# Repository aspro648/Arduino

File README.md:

# Arduino
DIY Clones done in KiCAD

- [Uno Compatible Through Hole](DIY%20Arduino/Arduino)
- [Leonardo Compatible Surface Mount](Leonardo/)

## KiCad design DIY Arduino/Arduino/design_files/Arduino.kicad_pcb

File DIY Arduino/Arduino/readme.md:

DIY Arduino clone done in KiCad.

You will need to build a FTDI breakout board using a FT231XQ QFN20 chip with a pinout matching the FT231XS (SSOP-20), but in a DIP-20 spacing.  It is all downhill from there!

Bill Of Materials
----------------
- 1 ea., DIY Arduino PCB from kicad.pcb file.
- 1 ea., FT231x breakout PCB from kicad.pcb file.
- 1 ea., U1 L7805CV IC REG LINEAR 5V 1.5A TO220AB, https://www.digikey.com/short/jn9qzp
- 1 ea., U2 FT231XQ 20QFN, https://www.digikey.com/short/jn57wn
- 1 ea., U3 SN74LS125AN, IC BUF NON-INVERT 5.25V 14DIP, https://www.digikey.com/short/jn973j
- 1 ea., U4 MCP1700-3302E/TO IC REG LINEAR 3.3V 250MA TO92-3, https://www.digikey.com/short/jn9q57
- 1 ea., U5 Atmega328P-PU https://www.digikey.com/short/jn57wj
- 1 ea., Y1 CER RES 16.0000MHZ 30PF T/H, ECS ZTT-16.00MX, https://www.digikey.com/short/jn9pjv
- 1 ea., C1 0.33uF 50V electrolytic Capacitor 2.5mm lead spacing, Nichicon 	UMT1HR33MDD1TP, https://www.digikey.com/short/jddb2h
- 4 ea., C2 - 5 CAP CER 0.1UF 25V Y5V RADIAL 2.5mm lead spacing, Vishay K104Z15Y5VE5TL2, https://www.digikey.com/short/jn9pm2
- 3 ea., C6 - 8 CAP CER 1UF 25V X7R RADIAL 5mm lead spacing, TDK FG28X7R1E105KRT06, https://www.digikey.com/short/jn9p97
- 1 ea., R1 4K7 Ohm Resistors 1/4 W 5%, https://www.digikey.com/short/jn5tmq
- 2 ea., R2, R13 1K Ohm Resistors 1/4 W 5%, https://www.digikey.com/short/jn5t4d
- 2 ea., R3 - 4 470 Ohm Resistors 1/4 W 5%, https://www.digikey.com/short/jn5tmp
- 2 ea., R5 - 6 22 Ohm Resistors 1/4 W 5%, https://www.digikey.com/short/jd0wcj
- 2 ea., R7 - 8 10K Resistors 1/4 W 5%, https://www.digikey.com/short/jn5t41
- 1 ea., D1 DIODE SCHOTTKY 40V 2A DO15, SMC SB240TA, https://www.digikey.com/short/jn57cv
- 1 ea., D2 (Power) Green 3mm LED 5.6mcd, LiteOn LTL-4231N https://www.digikey.com/short/jn5tr0
- 1 ea., D13 (D13) Red 3mm LED 4.4mcd, LiteOn LTL-4211N, https://www.digikey.com/short/jn5trr
- 2 ea., D3, D4 (TX/RX) Yellow 3mm LED 6.7mcd, LiteOn LTL-4251, https://www.digikey.com/short/jn5t5f
- 1 ea., F1 PTC RESET FUSE 30V 700MA RADIAL, Littlefuse RHEF070-2, https://www.digikey.com/short/pq0mtz
- 1 ea., J1 USB B Connector, Pulse E8144-B02022-L, https://www.digikey.com/short/jn571j
- 1 ea., J2 Barrel Jack 2.1mm, CUI 	PJ-202AH https://www.digikey.com/short/jd0wz3
- 2 ea., P1, P3 8-Pin header, https://www.digikey.com/short/jwj4dp
- 1 ea., P2 6-Pin header, https://www.digikey.com/short/jwj4w4
- 1 ea., P3 10-Pin header, https://www.digikey.com/short/jwj4n7
- 4 ea., Rubber feet, https://www.digikey.com/short/jntvm1 or https://www.digikey.com/short/jntvbz
- 1 ea., Pinheader, S1012EC-40-ND, https://www.digikey.com/short/7382z2
- 1 ea., CONN JUMPER SHORTING .100" GOLD, Sullins NPC02SXON-RC, https://www.digikey.com/short/jn5t0j
- 1 ea., 28 Pin socket, On Shore ED281DT, https://www.digikey.com/short/jn5tz5
- 1 ea., 20 Pin socket, On Shore ED20DT, https://www.digikey.com/short/jn5tzm
- 1 ea., 14 Pin socket, On Shore ED14DT, https://www.digikey.com/short/jn5tp1

License
----------------
[Attribution-ShareAlike 3.0 United States (CC BY-SA 3.0 US)](https://creativecommons.org/licenses/by-sa/3.0/us/)

You are free to:

- Share — copy and redistribute the material in any medium or format
- Adapt — remix, transform, and build upon the material

Under the following terms:

- Attribution — You must give appropriate credit, provide a link to the license, and indicate if changes were made. You may do so in any reasonable manner, but not in any way that suggests the licensor endorses you or your use.
- ShareAlike — If you remix, transform, or build upon the material, you must distribute your contributions under the same license as the original.

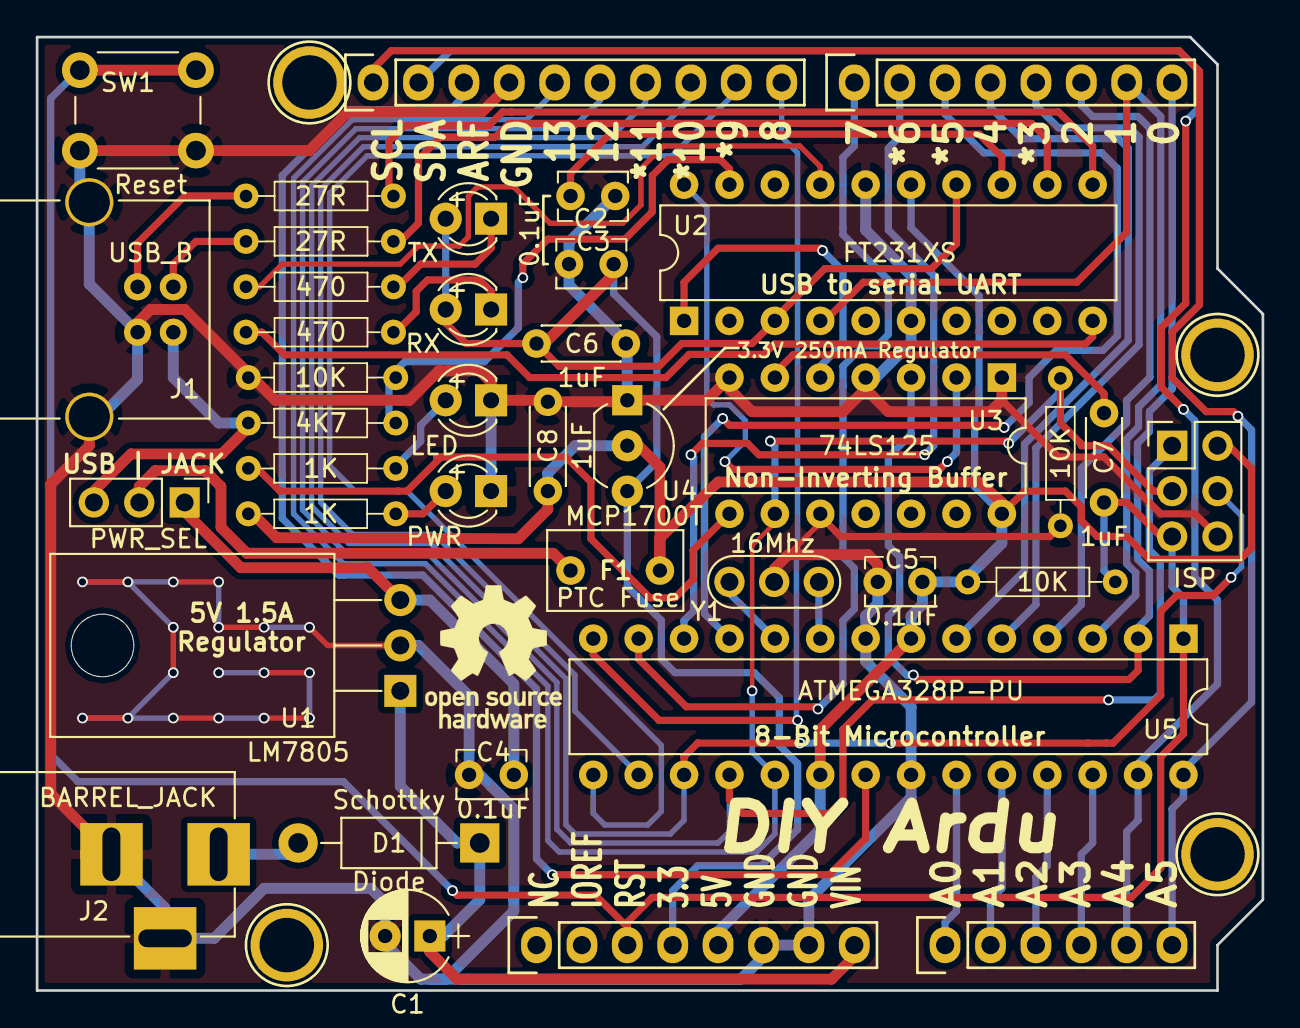
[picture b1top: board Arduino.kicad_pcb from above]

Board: 2 copper layers, 68.6 x 53.3 mm, 43 parts (0 on the bottom side), 48 nets.

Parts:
C1: 0.33uF; CP_Radial_D5.0mm_P2.50mm
C2, C3, C4, C5: 0.1uF; C_Disc_D3.8mm_W2.6mm_P2.50mm
C6, C7, C8: 1uF; C_Disc_D4.3mm_W1.9mm_P5.00mm
CON1: ISP; Pin_Header_Straight_2x03_Pitch2.54mm
D1: Schottky; D_DO-41_SOD81_P10.16mm_Horizontal
D2: PWR; LED_D3.0mm
D3: TX; LED_D3.0mm
D4: RX; LED_D3.0mm
D13: LED; LED_D3.0mm
F1: PTC Fuse; C_Disc_D7.5mm_W4.4mm_P5.00mm
J1: USB_B
J2: BARREL_JACK
J3: PWR_SEL; Pin_Header_Straight_1x03_Pitch2.54mm
P1: Power; Socket_Strip_Arduino_1x08
P2: Analog; Socket_Strip_Arduino_1x06
P3: Digital; Socket_Strip_Arduino_1x10
P4: Digital; Socket_Strip_Arduino_1x08
P5, P6, P7, P8: CONN_01X01; Arduino_1pin
R1: 4K7; R_Axial_DIN0204_L3.6mm_D1.6mm_P7.62mm_Horizontal
R2, R13: 1K; R_Axial_DIN0204_L3.6mm_D1.6mm_P7.62mm_Horizontal
R3, R4: 470; R_Axial_DIN0204_L3.6mm_D1.6mm_P7.62mm_Horizontal
R5, R6: 27R; R_Axial_DIN0204_L3.6mm_D1.6mm_P7.62mm_Horizontal
R7, R8, R9: 10K; R_Axial_DIN0204_L3.6mm_D1.6mm_P7.62mm_Horizontal
SW1: Reset; SW_PUSH_6mm
U1: LM7805; TO-220-3_Horizontal
U2: FT231XS; DIP-20_W7.62mm
U3: 74LS125; DIP-14_W7.62mm
U4: MCP1700T; TO-92_Inline_Wide
U5: ATMEGA328P-PU; DIP-28_W7.62mm
Y1: 16Mhz; Resonator-3pin_w7.0mm_h2.5mm

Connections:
+3V3: C3.1, C6.1, D3.2, D4.2, P1.4, U2.3, U2.14, U4.2
/0(RX): P4.8, U3.3, U5.2
/1(TX): P4.7, U2.4, U5.3
/2: P4.6, U5.4
/3(**): P4.5, U5.5
/4: P4.4, U5.6
/5(**): P4.3, U5.11
/6(**): P4.2, U5.12
/7: P4.1, U5.13
/8: P3.10, U5.14
/9(**): P3.9, U5.15
/10(SS): P3.8, U5.16
/11(MOSI): CON1.4, P3.7, U5.17
/12(MISO): CON1.1, P3.6, U5.18
/13(SCK): CON1.3, P3.5, R9.2, U3.9, U5.19
/A0: P2.1, U5.23
/A1: P2.2, U5.24
/A2: P2.3, U5.25
/A3: P2.4, U5.26
/A4(SDA): P2.5, P3.2, U5.27
/A5(SCL): P2.6, P3.1, U5.28
/AREF: P3.3, U5.21
/D+: J1.3, R5.2
/D-: J1.2, R6.2
/Reset: C7.1, CON1.5, P1.3, R8.1, SW1.2, U5.1
/USBVCC: J1.1, J3.3, R1.1
/Vin: C1.1, D1.1, P1.8, U1.1
GND: C1.2, C2.2, C3.2, C4.2, C5.2, C6.2, C8.2, CON1.6, D2.1, D13.1, J1.4, J1.5, J2.2, J2.3, P1.6, P1.7, P3.4, R7.1, R9.1, SW1.1, U1.2, U2.6, U2.16, U3.1, U3.4, U3.7, U3.10, U4.1, U5.8, U5.22, Y1.2
unnamed: C2.1, U2.13
unnamed: C4.1, J3.1, U1.3
unnamed: C7.2, U3.6
unnamed: D1.2, J2.1
unnamed: D2.2, R2.2
unnamed: D3.1, R3.1
unnamed: D4.1, R4.1
unnamed: D13.2, R13.2
unnamed: F1.1, J3.2
unnamed: R1.2, R7.2, U2.19
unnamed: R3.2, U2.17
unnamed: R4.2, U2.10
unnamed: R5.1, U2.11
unnamed: R6.1, U2.12
unnamed: R13.1, U3.8
unnamed: U2.1, U3.5
unnamed: U2.20, U3.2
unnamed: U5.9, Y1.3
unnamed: U5.10, Y1.1
VCC: C5.1, C8.1, CON1.2, F1.2, P1.5, R2.1, R8.2, U2.15, U3.14, U4.3, U5.7, U5.20

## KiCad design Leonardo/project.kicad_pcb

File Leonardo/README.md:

Leo, the Arduino Leonardo clone done in KiCad.

Bill Of Materials
----------------
  
- 1 ea., Perfect Purple PCB from OSH Park, with not so perfect layout from kicad.pcb file.
- 1 ea., U1 IC REG LINEAR 3.3V 150MA SOT23-5, LP2985-33DBVRG4, https://www.digikey.com/short/j29pqr
- 1 ea., U2 IC OPAMP GP 1MHZ RRO 8VSSOP, LM358DGKR, https://www.digikey.com/short/jnd53r
- 1 ea., U3 IC REG LINEAR 5V 1A SOT223 NCP1117ST50T3G, https://www.digikey.com/short/j29pqc
- 1 ea., U4 ATMEGA32U4-AU, IC MCU 8BIT 32KB FLASH 44TQFP, https://www.digikey.com/short/jb25pc
- 1 ea., Q1 MOSFET P-CH 20V 2A SSOT3, FDN340P, https://www.digikey.com/short/j29ppj

- 1 ea., Y1 CER RES 16.0000MHZ 15PF SMD, CSTCE16M0V53-R0, https://www.digikey.com/short/j2b9cm
- 2 ea., C1, C5 CAP CER 1UF SMD 0805
- 1 ea., C2 CAP CER 22pF SMD 0805
- 2 ea., C3, C6, C7 CAP CER 10UF 25V 1206, https://www.digikey.com/short/j29pwm
- 1 ea., C4 CAP CER 0.1UF SMD 0805

- 4 ea., D1-D4 SMD LED 0805, https://www.digikey.com/short/jwj4rb
- 1 ea., F1 PTC 1206, Bel 0ZCJ0025AF2E, https://www.digikey.com/short/jfcbc8
- 2 ea., RV1, RV2 VARISTOR 	VARISTOR 10.8V 40A 0805, https://www.digikey.com/short/jwj45d
- 4 ea., R1-R4 Resistor 1K OHM SMD 0805, https://www.digikey.com/short/j2d0wt
- 2 ea., R5, R8 Resistor 10K OHM SMD 0805, https://www.digikey.com/short/j2d0w4
- 2 ea., R6, R7 Resistor 22 OHM SMD 0805, https://www.digikey.com/short/jwj45j
- 1 ea., R9 Resistor 1M OHM SMD 0603, 

- 1 ea., SW1 (yellow) SWITCH TACTILE SPST-NO 0.05A 12V, SW416-ND, https://www.digikey.com/short/jwj4m9
- or (purple) KSEM31J LFS https://www.digikey.com/short/jnqh3m
- 1 ea., X3, CONN RCPT MICRO USB R/A SMD, Molex 1050170001, https://www.digikey.com/short/jb2205
- 1 ea., J1 Barrel Jack, https://www.digikey.com/short/j2fz43
- 1 ea., 6-Pin header, https://www.digikey.com/short/jwj4w4
- 2 ea., 8-Pin header, https://www.digikey.com/short/jwj4dp
- 1 ea., 10-Pin header, https://www.digikey.com/short/jwj4n7
- 1 ea., 2x3 Pin header, http://www.digikey.com/short/3m33n0

License
----------------
[Attribution-ShareAlike 3.0 United States (CC BY-SA 3.0 US)](https://creativecommons.org/licenses/by-sa/3.0/us/)

You are free to:

- Share — copy and redistribute the material in any medium or format
- Adapt — remix, transform, and build upon the material

Under the following terms:

- Attribution — You must give appropriate credit, provide a link to the license, and indicate if changes were made. You may do so in any reasonable manner, but not in any way that suggests the licensor endorses you or your use.
- ShareAlike — If you remix, transform, or build upon the material, you must distribute your contributions under the same license as the original.

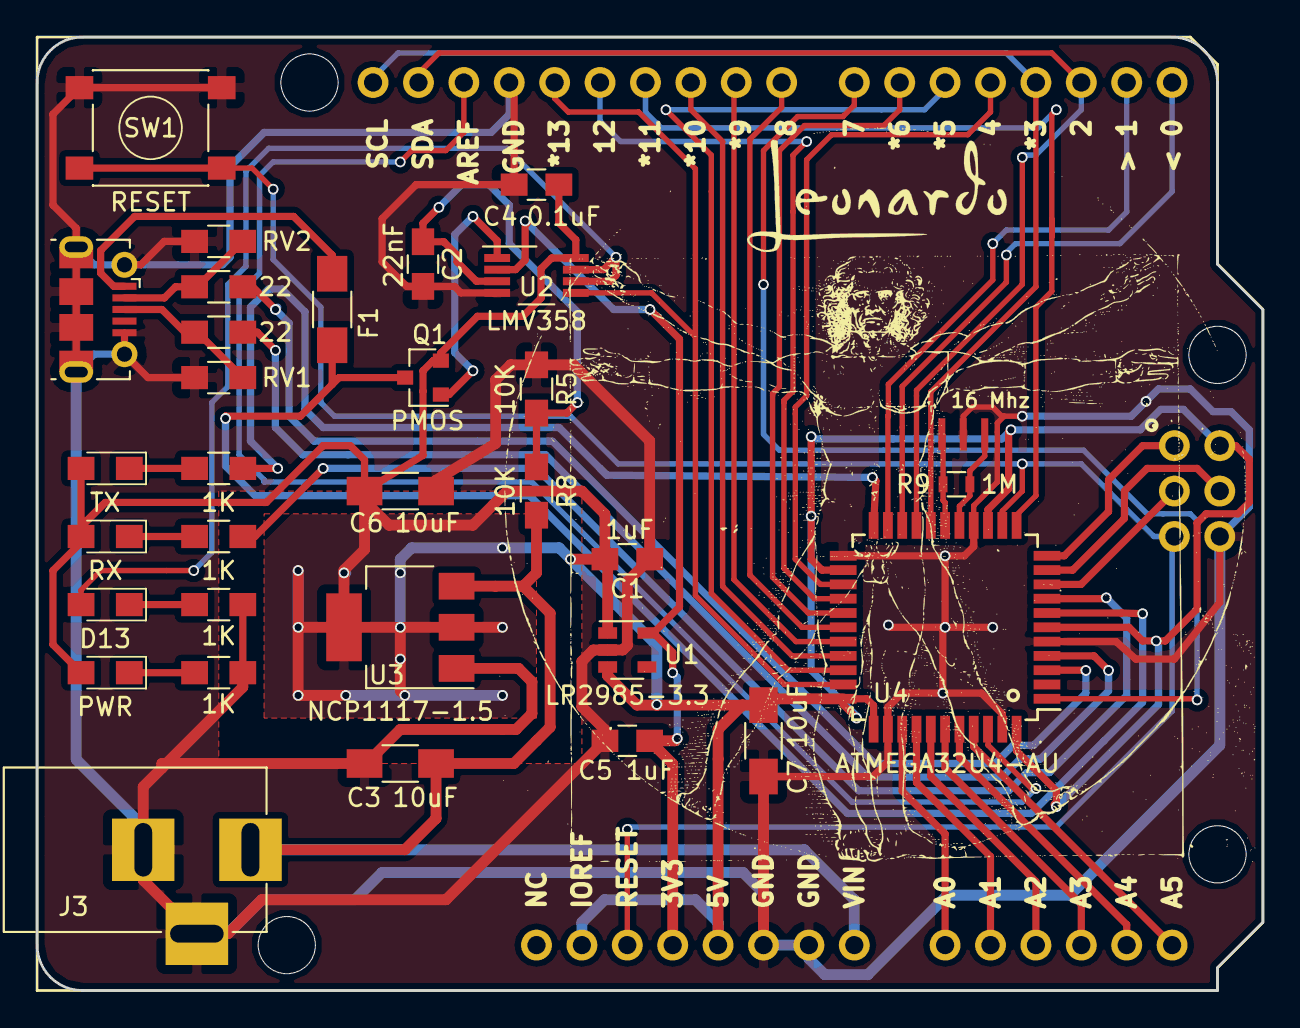
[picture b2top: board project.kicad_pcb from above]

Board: 2 copper layers, 68.6 x 53.3 mm, 34 parts (0 on the bottom side), 46 nets.

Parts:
C1, C5: 1uF; C_0805_HandSoldering
C2: 22nF; C_0805_HandSoldering
C3, C6, C7: 10uF; C_1206_HandSoldering
C4: 0.1uF; C_0805_HandSoldering
D1: PWR; LED_0805_HandSoldering
D2: TX; LED_0805_HandSoldering
D3: RX; LED_0805_HandSoldering
D4: D13; LED_0805_HandSoldering
F1: Polyfuse; R_1206_HandSoldering
J3: Barrel_Jack; BARREL_JACK
Q1: PMOS; SOT-23
R1, R2, R3, R4: 1K; R_0805_HandSoldering
R5, R8: 10K; R_0805_HandSoldering
R6, R7: 22; R_0805_HandSoldering
R9: 1M; R_0603
RV1, RV2: Varistor; R_0805_HandSoldering
SW1: RESET; SW_SPST_PTS645
U1: LP2985-3.3; SOT-23-5
U2: LMV358; VSSOP-8_3.0x3.0mm_Pitch0.65mm
U3: NCP1117-1.5; SOT-223-3_TabPin2
U4: ATMEGA32U4-AU; TQFP-44_10x10mm_Pitch0.8mm
VAL: MadeInOregonRev25
X1: USB_OTG; USB_Micro-B_Molex-105017-0001
XA1: Arduino_Leonardo_Shield
Y1: 16 Mhz; Resonator_SMD_CTSC_1.3mmx3.2mm

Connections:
+3V3: C5.1, U1.5, U2.2, XA1.3V3
+5V: C1.1, C4.1, C6.1, C7.1, D1.2, D2.2, D3.2, Q1.2, U1.1, U1.3, U2.8, U3.2, U4.6, U4.14, U4.24, U4.33, U4.34, U4.44, XA1.5V1, XA1.5V2, XA1.IORF
/A0: U4.36, XA1.A0
/A1: U4.37, XA1.A1
/A2: U4.38, XA1.A2
/A3: U4.39, XA1.A3
/A4: U4.40, XA1.A4
/A5: U4.41, XA1.A5
/AREF: U4.42, XA1.AREF
/D0: U4.20, XA1.D0
/D1: U4.21, XA1.D1
/D4: U4.25, XA1.D4
/D5: U4.31, XA1.D5
/D6: U4.27, XA1.D6
/D7: U4.1, XA1.D7
/D8: U4.28, XA1.D8
/D9: U4.29, XA1.D9
/D10: U4.30, XA1.D10
/D11: U4.12, XA1.D11
/D12: U4.26, XA1.D12
/D13: U2.5, U4.32, XA1.D13
/D+: R6.1, U4.4
/D-: R7.1, U4.3
/MISO: U4.11, XA1.MISO
/MOSI: U4.10, XA1.MOSI
/RXLED: R3.1, U4.8
/SCK: U4.9, XA1.SCK
/SCL: U4.18, XA1.D3, XA1.SCL
/SDA: U4.19, XA1.D2, XA1.SDA
/TXLED: R2.1, U4.22
/VIN: C3.1, J3.1, R8.2, U3.3, XA1.VIN
/~RESET: SW1.2, U4.13, XA1.RST1, XA1.RST2
GND: C1.2, C2.2, C3.2, C4.2, C5.2, C6.2, C7.2, J3.2, J3.3, R1.2, R4.2, R5.1, RV1.2, RV2.2, SW1.1, U1.2, U2.4, U3.1, U4.5, U4.15, U4.23, U4.35, U4.43, X1.5, X1.6, XA1.GND1, XA1.GND2, XA1.GND3, XA1.GND4, Y1.2
unnamed: C2.1, R5.2, R8.1, U2.3
unnamed: D1.1, R1.1
unnamed: D2.1, R2.2
unnamed: D3.1, R3.2
unnamed: D4.1, R4.1
unnamed: D4.2, U2.6, U2.7
unnamed: F1.2, X1.1
unnamed: Q1.1, U2.1
unnamed: R6.2, RV1.1, X1.3
unnamed: R7.2, RV2.1, X1.2
unnamed: R9.1, U4.16, Y1.3
unnamed: R9.2, U4.17, Y1.1
VBUS: F1.1, Q1.3, U4.7

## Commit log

2018-10-28 Initial upload
2018-10-28 Updating Leonardo
2018-10-31 Minor footprint tweaks
2019-03-18 documents update
